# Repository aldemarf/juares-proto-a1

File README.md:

# juares-proto-a1
Juá AMS prototype running on Arduino Framework based on ESP32 T-Beam board, MPU6050, and SD Card.

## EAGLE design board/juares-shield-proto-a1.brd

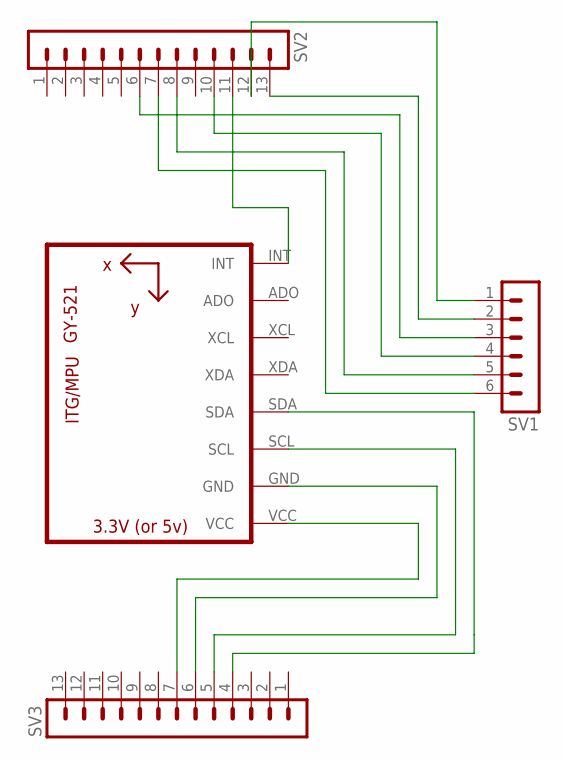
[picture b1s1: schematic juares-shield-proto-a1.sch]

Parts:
SV1: MA06-1
SV2, SV3: MA13-1
U1: GY-521MPU6050; GY-521

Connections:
unnamed: SV2.11, U1.INT
unnamed: SV3.4, U1.SDA
unnamed: SV3.6, U1.GND
unnamed: SV3.7, U1.VCC
unnamed: SV1.3, SV2.6
unnamed: SV1.1, SV2.12
unnamed: SV1.2, SV2.13
unnamed: SV1.4, SV2.10
unnamed: SV1.5, SV2.8
unnamed: SV1.6, SV2.7
unnamed: SV3.5, U1.SCL

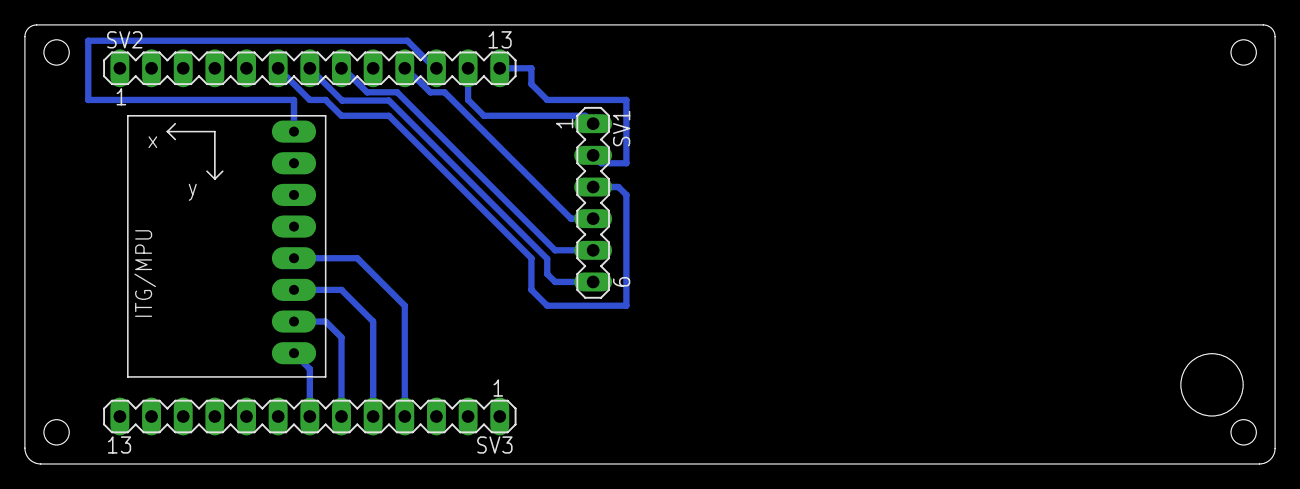
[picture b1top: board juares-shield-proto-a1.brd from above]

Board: 2 copper layers, 100.3 x 35.2 mm, 4 parts (0 on the bottom side), 11 nets.

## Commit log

2019-07-12 currentversion of the esp32 prototype
2019-07-19 integration with i2cdev mpu6050
2019-07-19 integration i2cdevlib
2019-08-08 first version with power management
2019-08-18 improving code modularization - created SDUtil class
2019-08-20 MPUUtil class creation
2019-09-03 board design files and power improvements
2019-09-03 power management improvements
2019-09-03 power improvements
2019-09-05 mpu and gps modifications
2019-09-05 gps integration
2019-09-06 smal adjusts
2019-09-06 lora insertion
2019-09-06 lora corrections
2019-09-06 versao utilizada em campo no experimento 1 - 2019-08-01
2019-09-06 versao lora com problema no scheduler
2019-11-14 experimento de lucas tcc - v0.1
